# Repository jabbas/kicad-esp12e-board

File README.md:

# An ESP8266-12e Board compatible with ESP-01/ESP-01S with additional IO and 5V to 3.3V Voltage Regulator

# Schema

# Renders

## Front

## Back

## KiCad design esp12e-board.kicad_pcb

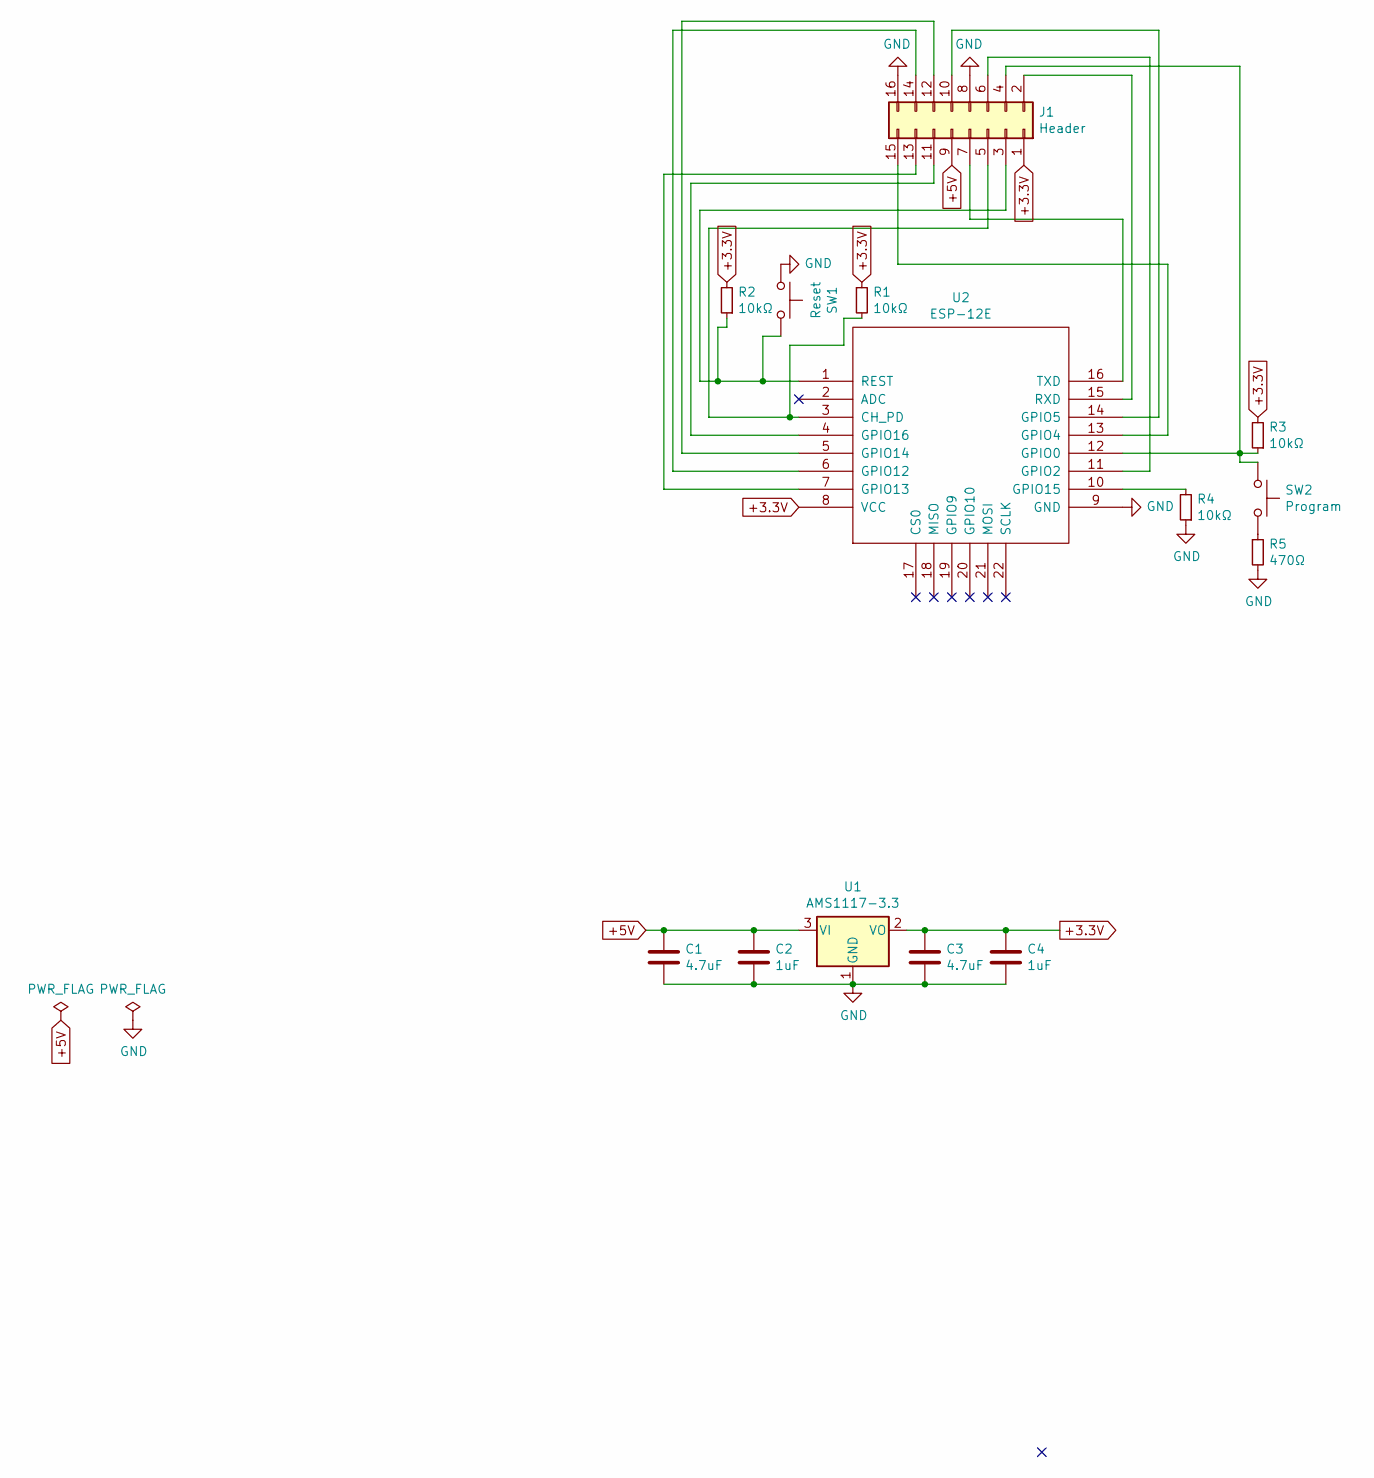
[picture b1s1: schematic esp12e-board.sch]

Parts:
C1, C3: 4.7uF; C_0805_2012Metric_Pad1.15x1.40mm_HandSolder
C2, C4: 1uF; C_0805_2012Metric_Pad1.15x1.40mm_HandSolder
J1: Header; PinHeader_2x08_P2.54mm_Vertical
R1, R2, R3, R4: 10kΩ; R_0805_2012Metric_Pad1.15x1.40mm_HandSolder
R5: 470Ω; R_0805_2012Metric_Pad1.15x1.40mm_HandSolder
SW1: Reset; SW_SPST_B3U-1000P-B
SW2: Program; SW_SPST_B3U-1000P-B
U1: AMS1117-3.3; SOT-223-3_TabPin2
U2: ESP-12E; ESP-12E_SMD

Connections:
+3.3V: C3.1, C4.1, J1.1, R1.1, R2.2, R3.2, U1.2 (VO), U2.8 (VCC)
+5V: C1.1, C2.1, J1.9, U1.3 (VI)
GND: C1.2, C2.2, C3.2, C4.2, J1.8, J1.16, R4.1, R5.2, SW1.1, U1.1 (GND), U2.9 (GND)
unnamed: J1.2, U2.15 (RXD)
unnamed: J1.3, R2.1, SW1.2, U2.1 (REST)
unnamed: J1.4, R3.1, SW2.1, U2.12 (GPIO0)
unnamed: J1.5, R1.2, U2.3 (CH_PD)
unnamed: J1.6, U2.11 (GPIO2)
unnamed: J1.7, U2.16 (TXD)
unnamed: J1.10, U2.14 (GPIO5)
unnamed: J1.11, U2.4 (GPIO16)
unnamed: J1.12, U2.5 (GPIO14)
unnamed: J1.13, U2.7 (GPIO13)
unnamed: J1.14, U2.6 (GPIO12)
unnamed: J1.15, U2.13 (GPIO4)
unnamed: R4.2, U2.10 (GPIO15)
unnamed: R5.1, SW2.2

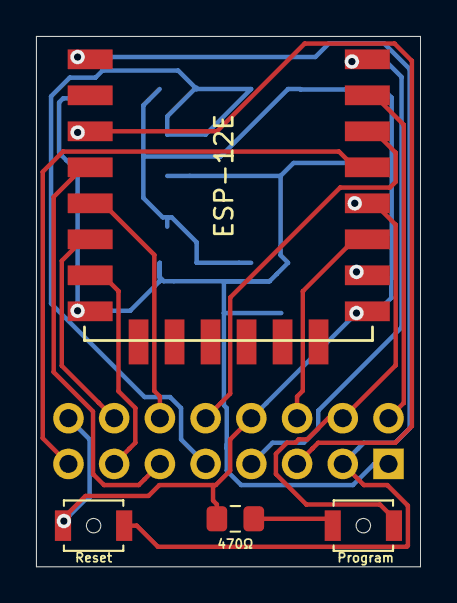
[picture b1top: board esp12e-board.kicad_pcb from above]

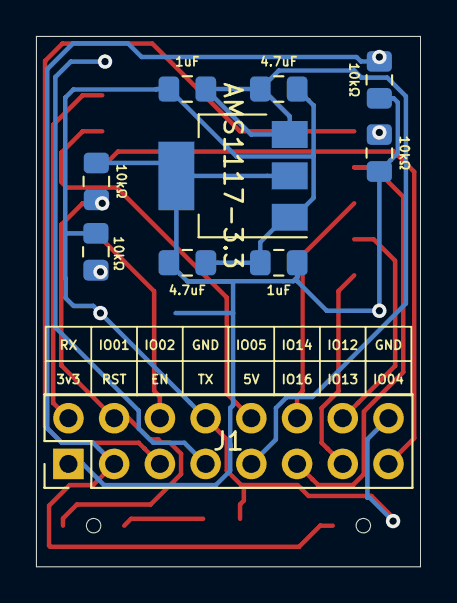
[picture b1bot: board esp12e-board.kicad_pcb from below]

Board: 2 copper layers, 21.3 x 29.5 mm, 14 parts (10 on the bottom side), 17 nets.

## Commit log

2020-01-29 First version sent to fab
2020-02-27 updates gitignore
2020-02-27 adds necessary pull up/down resistors to pins to be able to boot
2020-02-27 rewiring and changed pads to switches
2020-02-28 replaces buttons with THT ones
2020-04-14 fixes booting - io15 should be pulled down
